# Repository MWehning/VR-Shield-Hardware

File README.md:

View full project at:
https://www.openhardware.io/view/33050

## Kicad files required to replicate the VR-Shield PCB. 

# Required components:

* SMD-Resistors (0805)

  * 1x 120 Ohm
  
  * 1x 3.3k Ohm
  
  * 1x 33k Ohm
  
* 1x LED Blue (0805)

* 1x IRF7404 Mosfet (SOIC 8)

* 1x BC847 NPN Transistor (SOT 23)

* 1x ESP32 WROOM32 Devkit C

* 2x 02x08 angled pin header (2.54mm, middle two rows need to be removed to form two 02x03 sockets)

## Build instructions can be found at /bom/ibom.html

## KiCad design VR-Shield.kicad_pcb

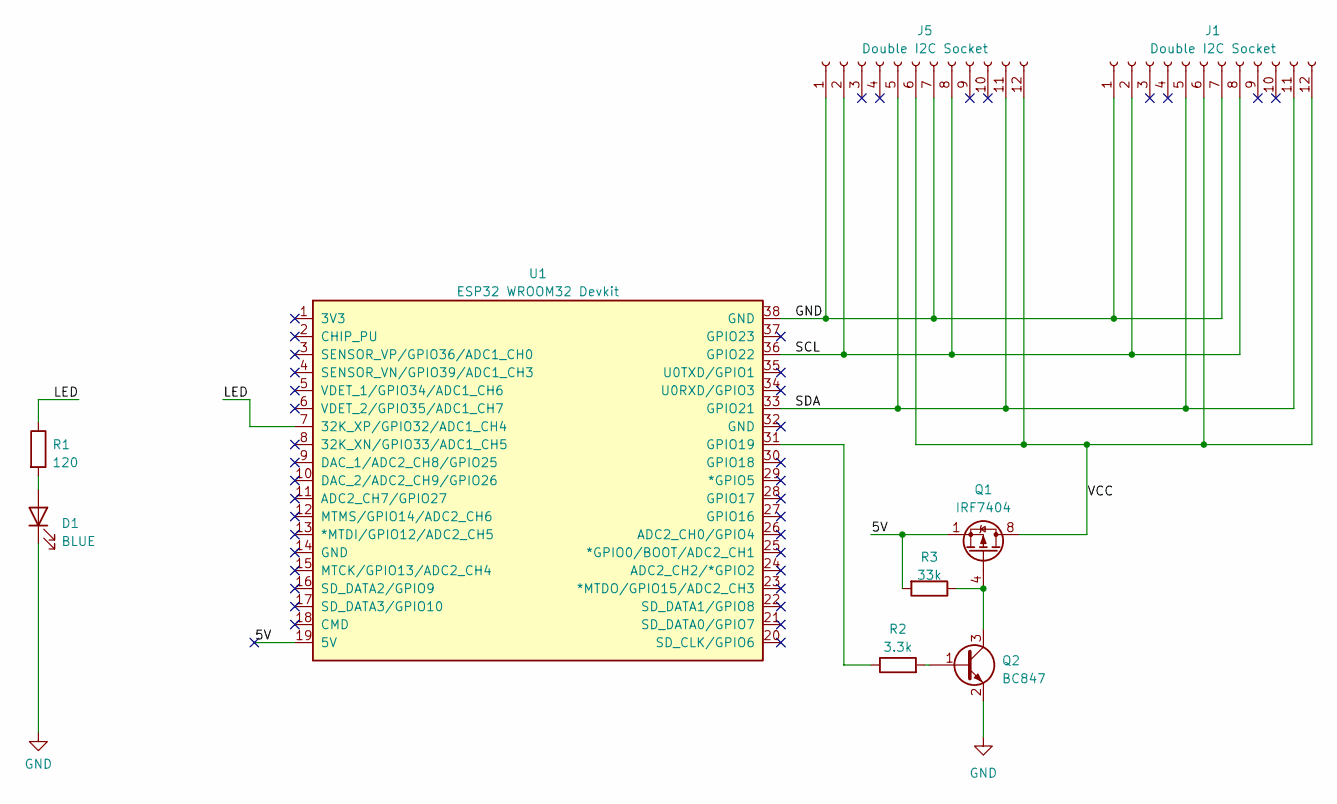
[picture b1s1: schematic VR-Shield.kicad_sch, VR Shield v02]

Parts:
D1: BLUE; LED_0805_2012Metric_Pad1.15x1.40mm_HandSolder
J1, J5: Double I2C Socket; Custom Socket I2C
Q1: IRF7404; SOIC-8_3.9x4.9mm_P1.27mm
Q2: BC847; SOT-23
R1: 120; R_0805_2012Metric_Pad1.20x1.40mm_HandSolder
R2: 3.3k; R_0805_2012Metric_Pad1.20x1.40mm_HandSolder
R3: 33k; R_0805_2012Metric_Pad1.20x1.40mm_HandSolder
U1: ESP32 WROOM32 Devkit; ESP32-DevKitC

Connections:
/5V: Q1.1 (S), Q1.2 (S), Q1.3 (S), R3.2, U1.19 (5V)
/LED: R1.1, U1.7 (32K_XP/GPIO32/ADC1_CH4)
/SCL: J1.2, J1.8, J5.2, J5.8, U1.36 (GPIO22)
/SDA: J1.5, J1.11, J5.5, J5.11, U1.33 (GPIO21)
/VCC: J1.6, J1.12, J5.6, J5.12, Q1.5 (D), Q1.6 (D), Q1.7 (D), Q1.8 (D)
GND: D1.1 (K), J1.1, J1.7, J5.1, J5.7, Q2.2 (E), U1.38 (GND)
unnamed: D1.2 (A), R1.2
unnamed: Q1.4 (G), Q2.3 (C), R3.1
unnamed: Q2.1 (B), R2.2
unnamed: R2.1, U1.31 (GPIO19)

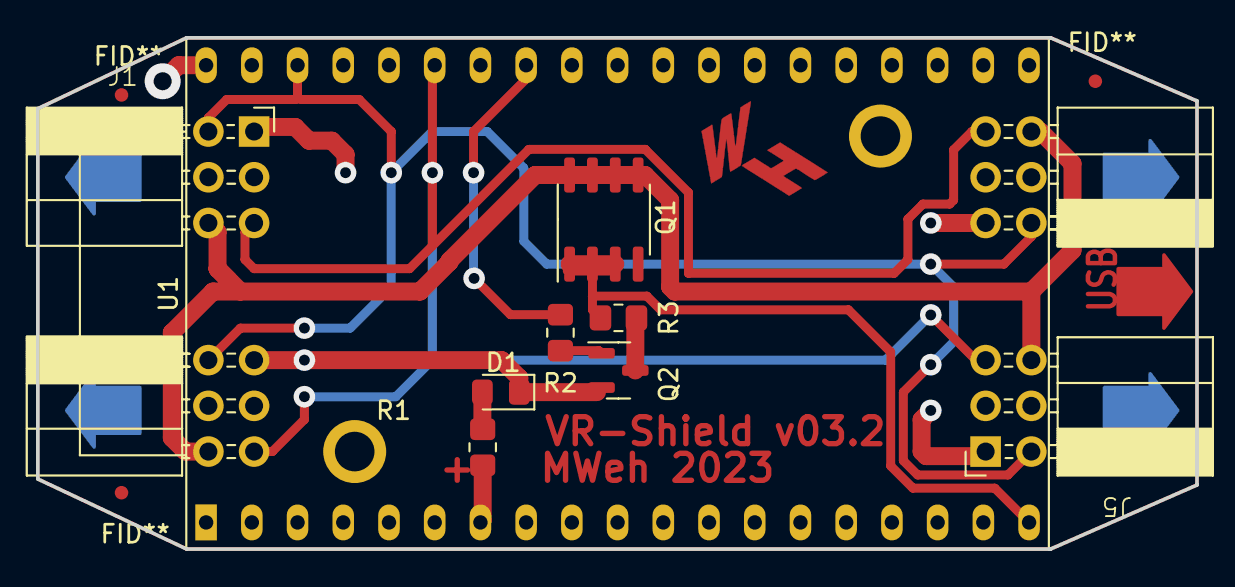
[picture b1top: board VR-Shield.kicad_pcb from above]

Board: 2 copper layers, 64.4 x 28.4 mm, 12 parts (0 on the bottom side), 10 nets.

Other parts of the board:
FID**: Fiducial_0.75mm_Mask1.5mm
FID**#2, FID**#3: Fiducial_0.75mm_Mask1.5mm

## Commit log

2023-03-01 Commit to github
2023-03-07 Fixed issues with pad size and distance Please enter the commit message for your changes. Lines starting
2023-04-17 t V03!!!!
2023-05-15 User friendlyness improved
2023-05-15 Attempt to push
2023-05-15 Create LICENSE
2023-05-15 Added BOM

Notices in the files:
VR-Shield.kicad_pcb:
License: Apache 2.0
VR-Shield.kicad_sch:
creativecommons.org/licenses/by/4.0
License: CC BY 4.0
